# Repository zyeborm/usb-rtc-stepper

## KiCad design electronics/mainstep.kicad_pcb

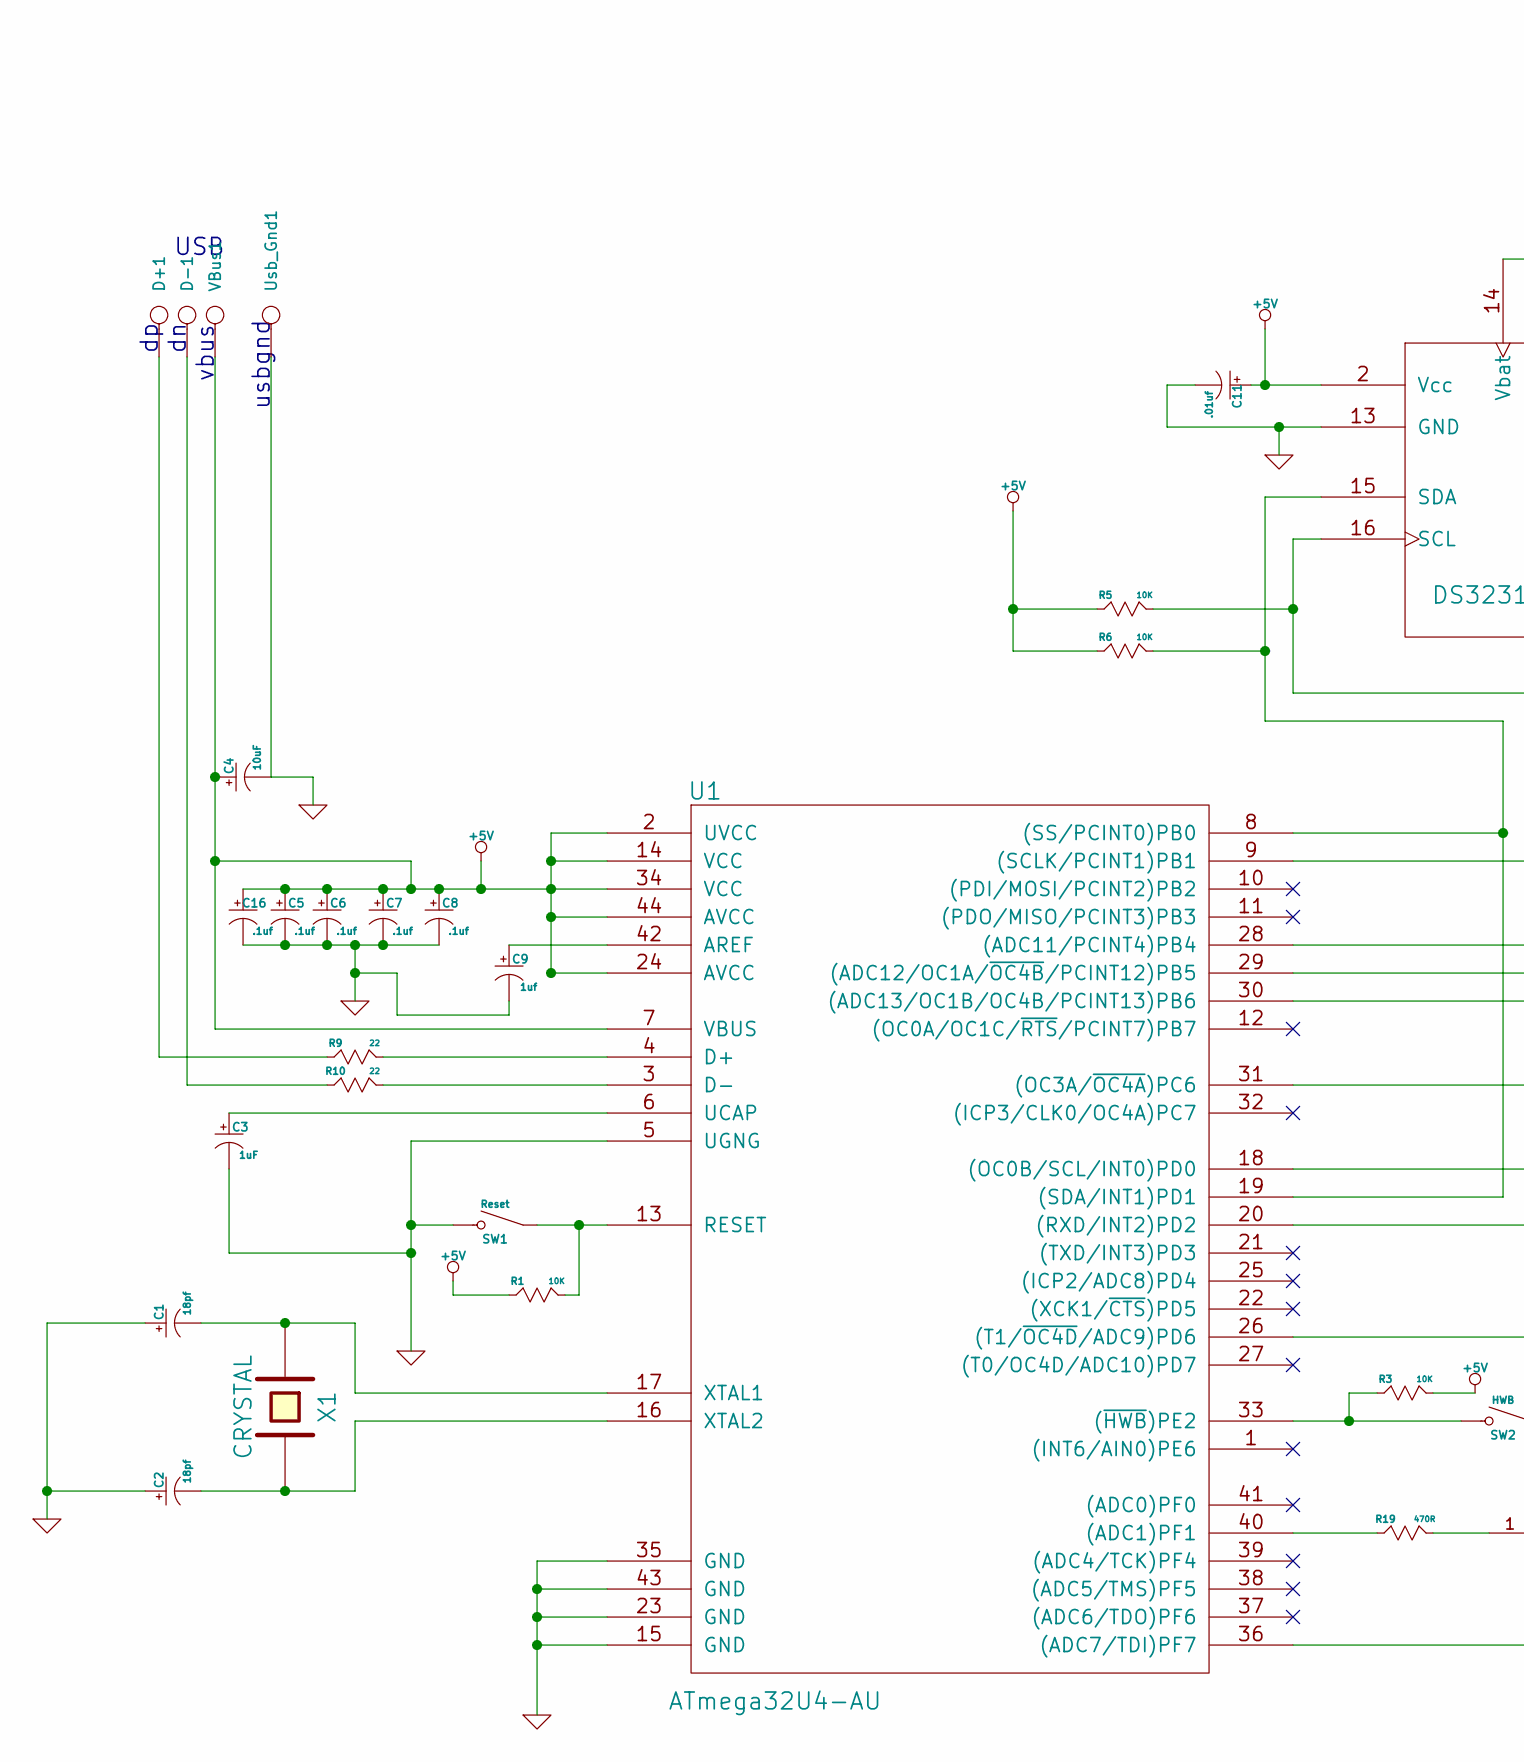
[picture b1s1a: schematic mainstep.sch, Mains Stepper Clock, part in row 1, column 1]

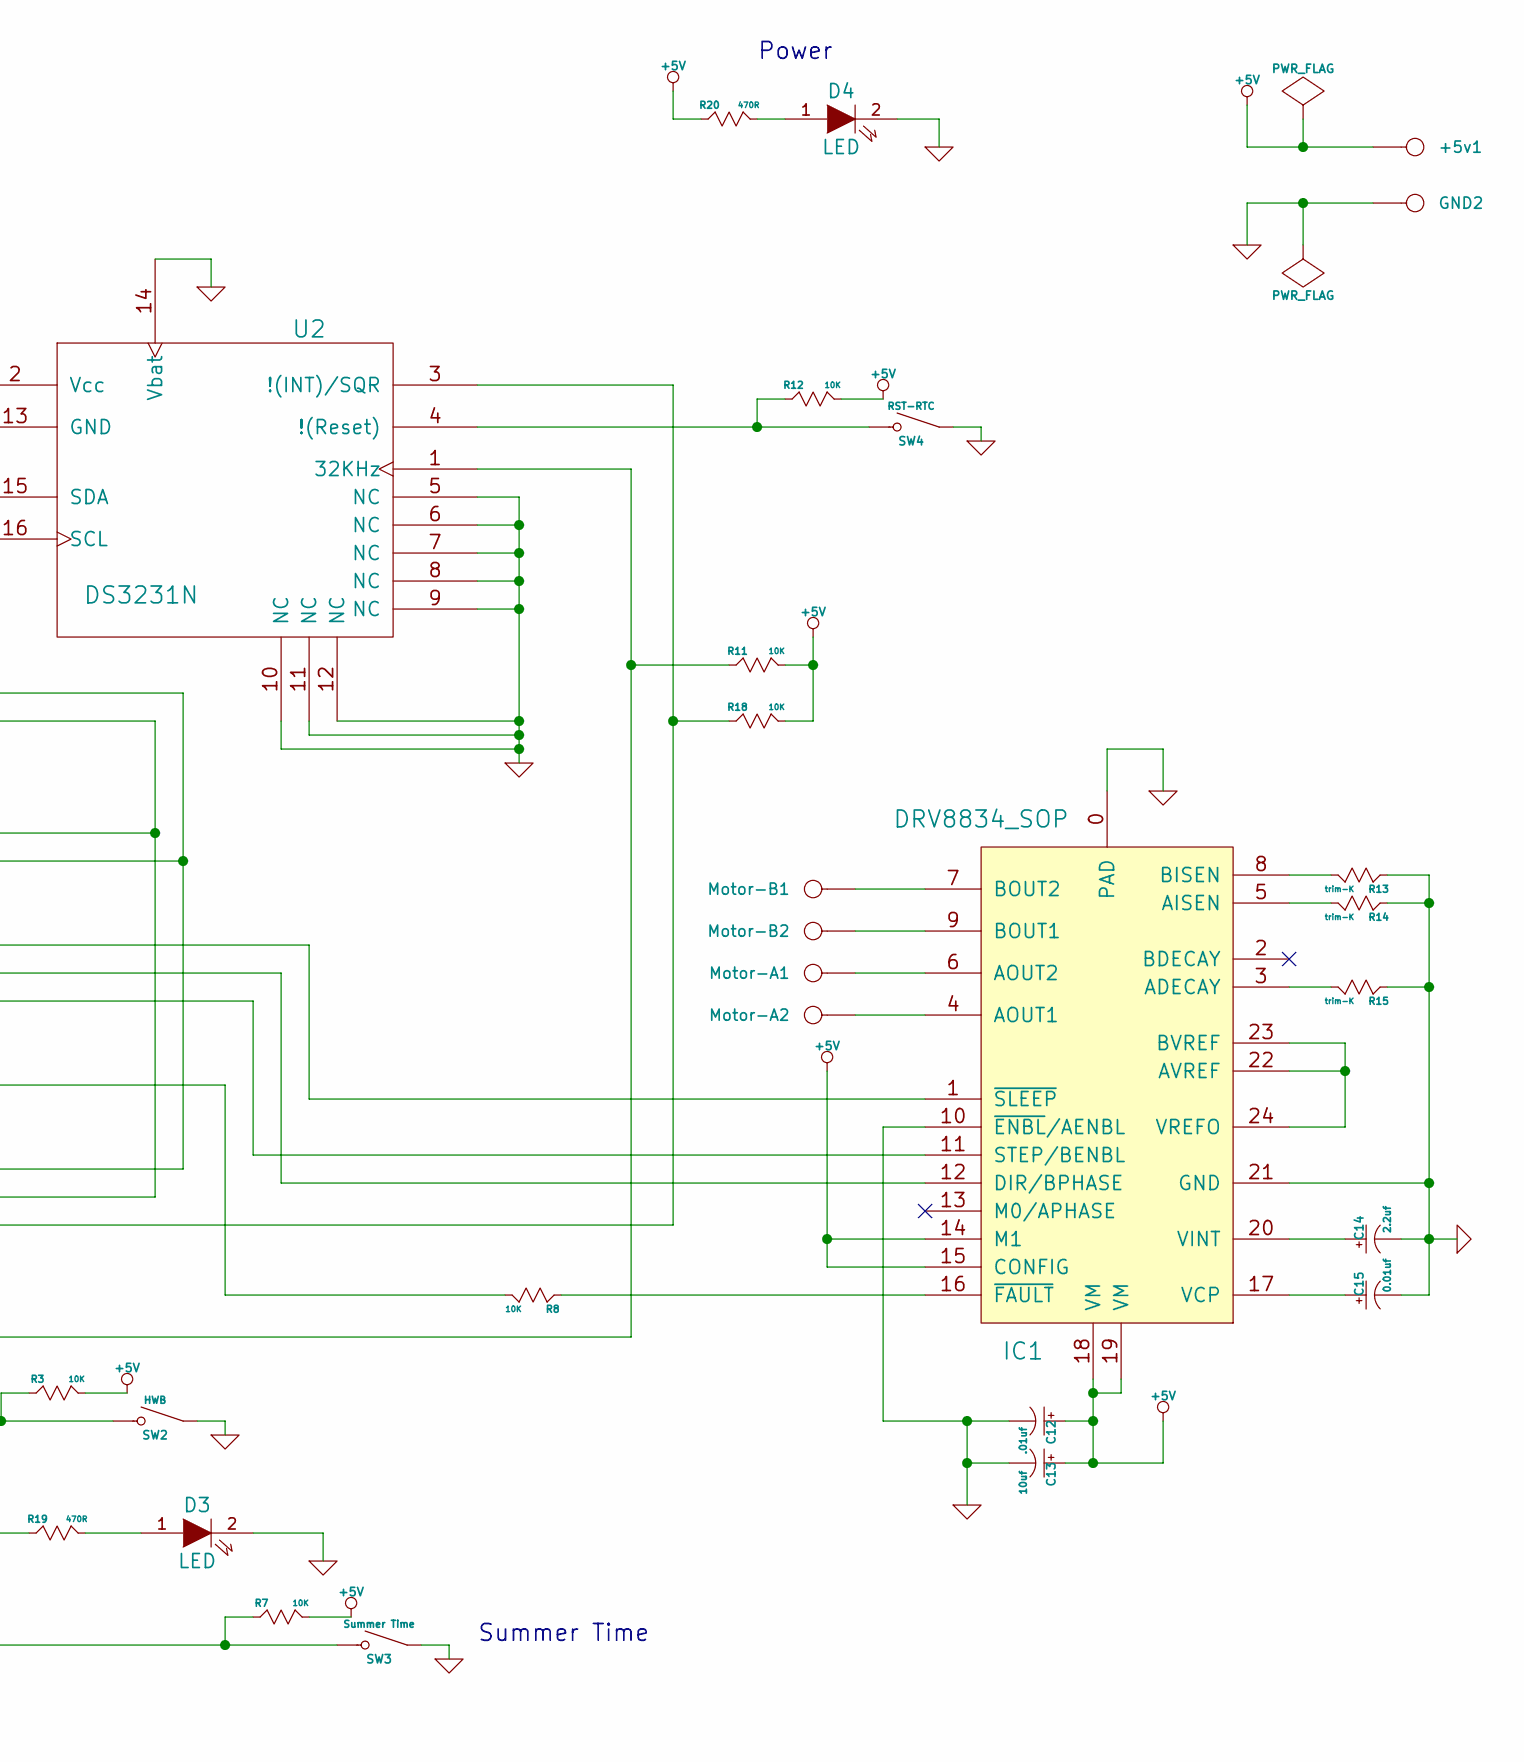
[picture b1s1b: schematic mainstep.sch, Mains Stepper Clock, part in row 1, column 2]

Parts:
+5v1: CONN_1
C1, C2: 18pf
C3: 1uF
C4: 10uF
C5, C6, C7, C8, C16: .1uf
C9: 1uf
C11, C12: .01uf
C13: 10uf
C14: 2.2uf
C15: 0.01uf
D3, D4: LED
D+1: CONN_1
D-1: CONN_1
GND2: CONN_1
IC1: DRV8834_SOP
Motor-A1, Motor-A2: CONN_1
Motor-B1, Motor-B2: CONN_1
R1, R3, R5, R6, R7, R8, R11, R12, R18: 10K
R9, R10: 22
R13, R14, R15: trim-K
R19, R20: 470R
SW1: Reset
SW2: HWB
SW3: Summer Time
SW4: RST-RTC
U1: ATmega32U4-AU
U2: DS3231N
Usb_Gnd1: CONN_1
VBus1: CONN_1
X1: CRYSTAL

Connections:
+5V: +5v1.1, C4.2, C5.2, C6.2, C7.2, C8.2, C11.2, C12.2, C13.2, C16.2, IC1.14 (M1), IC1.15 (CONFIG), IC1.18 (VM), IC1.19 (VM), R1.2 (B), R3.1 (A), R5.2 (B), R6.2 (B), R7.1 (A), R11.1 (A), R12.1 (A), R18.1 (A), R20.2 (B), U1.2 (UVCC), U1.7 (VBUS), U1.14 (VCC), U1.24 (AVCC), U1.34 (VCC), U1.44 (AVCC), U2.2 (Vcc), VBus1.1
GND: C1.2, C2.2, C3.1 (GND), C4.1 (GND), C5.1 (GND), C6.1 (GND), C7.1 (GND), C8.1 (GND), C9.1 (GND), C11.1 (GND), C12.1 (GND), C13.1 (GND), C14.1 (GND), C15.1 (GND), C16.1 (GND), D3.2 (K), D4.2 (K), GND2.1, IC1.0 (PAD), IC1.10 (~ENBL~/AENBL), IC1.21 (GND), R13.2 (B), R14.2 (B), R15.2 (B), SW1.1 (A), SW2.2 (B), SW3.2 (B), SW4.2 (B), U1.5 (UGNG), U1.15 (GND), U1.23 (GND), U1.35 (GND), U1.43 (GND), U2.5 (NC), U2.6 (NC), U2.7 (NC), U2.8 (NC), U2.9 (NC), U2.10 (NC), U2.11 (NC), U2.12 (NC), U2.13 (GND), U2.14 (Vbat), Usb_Gnd1.1
unnamed: C1.1 (GND), U1.17 (XTAL1), X1.1
unnamed: C2.1 (GND), U1.16 (XTAL2), X1.2
unnamed: C3.2, U1.6 (UCAP)
unnamed: C9.2, U1.42 (AREF)
unnamed: C14.2, IC1.20 (VINT)
unnamed: C15.2, IC1.17 (VCP)
unnamed: D3.1 (A), R19.1 (A)
unnamed: D4.1 (A), R20.1 (A)
unnamed: D+1.1, R9.2 (B)
unnamed: D-1.1, R10.2 (B)
unnamed: IC1.1 (~SLEEP~), U1.28 ((ADC11/PCINT4)PB4)
unnamed: IC1.3 (ADECAY), R15.1 (A)
unnamed: IC1.4 (AOUT1), Motor-A2.1
unnamed: IC1.5 (AISEN), R14.1 (A)
unnamed: IC1.6 (AOUT2), Motor-A1.1
unnamed: IC1.7 (BOUT2), Motor-B1.1
unnamed: IC1.8 (BISEN), R13.1 (A)
unnamed: IC1.9 (BOUT1), Motor-B2.1
unnamed: IC1.11 (STEP/BENBL), U1.30 ((ADC13/OC1B/OC4B/PCINT13)PB6)
unnamed: IC1.12 (DIR/BPHASE), U1.29 ((ADC12/OC1A/~OC4B~/PCINT12)PB5)
unnamed: IC1.16 (~FAULT~), R8.2 (B)
unnamed: IC1.22 (AVREF), IC1.23 (BVREF), IC1.24 (VREFO)
unnamed: R1.1 (A), SW1.2 (B), U1.13 (RESET)
unnamed: R3.2 (B), SW2.1 (A), U1.33 ((~HWB~)PE2)
unnamed: R5.1 (A), U1.9 ((SCLK/PCINT1)PB1), U1.18 ((OC0B/SCL/INT0)PD0), U2.16 (SCL)
unnamed: R6.1 (A), U1.8 ((SS/PCINT0)PB0), U1.19 ((SDA/INT1)PD1), U2.15 (SDA)
unnamed: R7.2 (B), SW3.1 (A), U1.36 ((ADC7/TDI)PF7)
unnamed: R8.1 (A), U1.31 ((OC3A/~OC4A~)PC6)
unnamed: R9.1 (A), U1.4 (D+)
unnamed: R10.1 (A), U1.3 (D-)
unnamed: R11.2 (B), U1.26 ((T1/~OC4D~/ADC9)PD6), U2.1 (32KHz)
unnamed: R18.2 (B), U1.20 ((RXD/INT2)PD2), U2.3 (!(INT)/SQR)
unnamed: R19.2 (B), U1.40 ((ADC1)PF1)

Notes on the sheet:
vbus
usbgnd
USB
Summer Time
Power

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
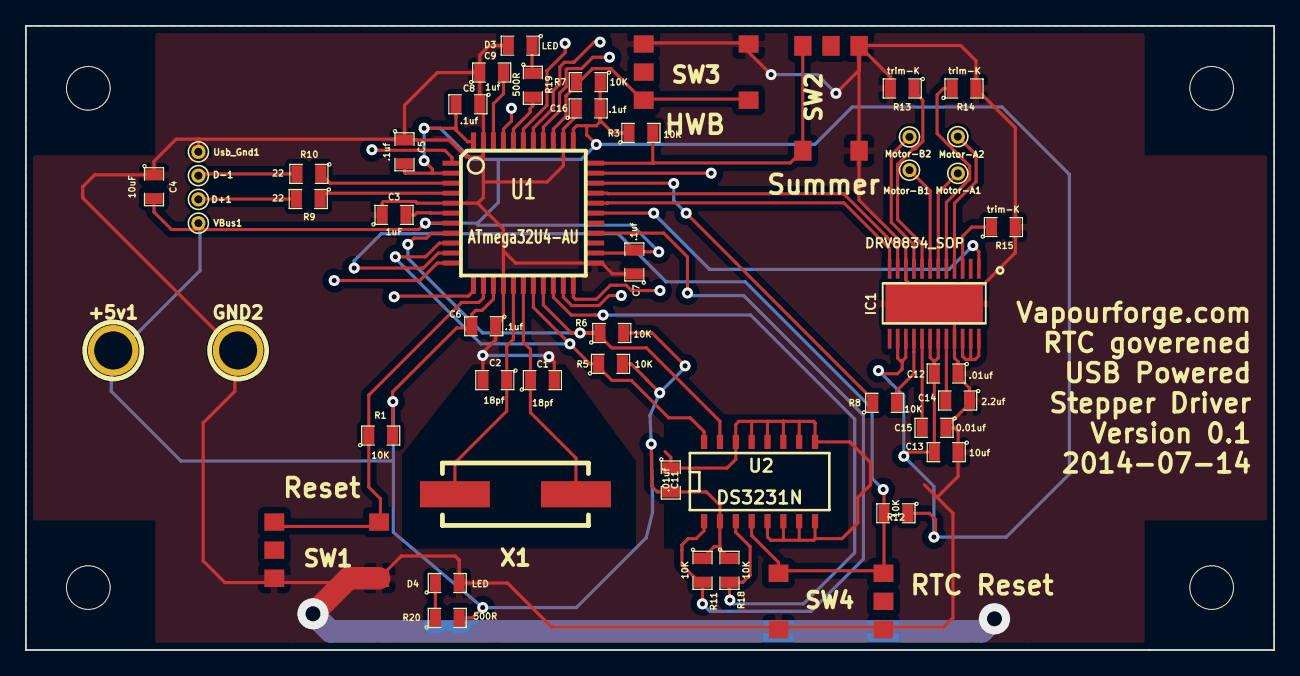
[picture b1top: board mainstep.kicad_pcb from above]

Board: 2 copper layers, 100.0 x 50.0 mm, 51 parts (0 on the bottom side), 36 nets.

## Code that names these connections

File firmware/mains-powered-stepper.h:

/*
             LUFA Library
     Copyright (C) Dean Camera, 2013.

  dean [at] fourwalledcubicle [dot] com
           www.lufa-lib.org
*/

/*
  Copyright 2013  Dean Camera (dean [at] fourwalledcubicle [dot] com)

  Permission to use, copy, modify, distribute, and sell this
  software and its documentation for any purpose is hereby granted
  without fee, provided that the above copyright notice appear in
  all copies and that both that the copyright notice and this
  permission notice and warranty disclaimer appear in supporting
  documentation, and that the name of the author not be used in
  advertising or publicity pertaining to distribution of the
  software without specific, written prior permission.

  The author disclaims all warranties with regard to this
  software, including all implied warranties of merchantability
  and fitness.  In no event shall the author be liable for any
  special, indirect or consequential damages or any damages
  whatsoever resulting from loss of use, data or profits, whether
  in an action of contract, negligence or other tortious action,
  arising out of or in connection with the use or performance of
  this software.
*/

/** \file
 *
 *  Header file for VirtualSerial.c.
 */

#ifndef _VIRTUALSERIAL_H_
#define _VIRTUALSERIAL_H_

	/* Includes: */
		#include <avr/io.h>
		#include <avr/wdt.h>
		#include <avr/power.h>
		#include <avr/interrupt.h>
		#include <string.h>
		#include <stdio.h>
    #include "avr035.h"
		#include "Descriptors.h"

		//#include <LUFA/Drivers/Board/LEDs.h>
		//#include <LUFA/Drivers/Board/Joystick.h>
		#include <LUFA/Drivers/USB/USB.h>

	/* Macros: */
		/** LED mask for the library LED driver, to indicate that the USB interface is not ready. */
		#define LEDMASK_USB_NOTREADY      LEDS_LED1

		/** LED mask for the library LED driver, to indicate that the USB interface is enumerating. */
		#define LEDMASK_USB_ENUMERATING  (LEDS_LED2 | LEDS_LED3)

		/** LED mask for the library LED driver, to indicate that the USB interface is ready. */
		#define LEDMASK_USB_READY        (LEDS_LED2 | LEDS_LED4)

		/** LED mask for the library LED driver, to indicate that an error has occurred in the USB interface. */
		#define LEDMASK_USB_ERROR        (LEDS_LED1 | LEDS_LED3)

	/* Function Prototypes: */
		void SetupHardware(void);
		void CheckJoystickMovement(void);

		void EVENT_USB_Device_Connect(void);
		void EVENT_USB_Device_Disconnect(void);
		void EVENT_USB_Device_ConfigurationChanged(void);
		void EVENT_USB_Device_ControlRequest(void);
		
  #define FLASHER_PORT  PORTF 
  #define FLASHER_PIN   PF1
  #define FLASHER_DDR   DDRF
  #define FLASHER_LED  FLASHER_PORT, FLASHER_PIN  		

  
  #define TIMER1_PWM_PORT  PORTB
  #define TIMER1_PWM_PIN   PB6
  #define TIMER1_PWM_DDR   DDRB
  #define TIMER1_PWM  TIMER1_PWM_PORT, TIMER1_PWM_PIN  		

  #define SLEEP_PORT  PORTB
  #define SLEEP_PIN   PB4
  #define SLEEP_DDR   DDRB
  #define SLEEP_DRV  SLEEP_PORT, SLEEP_PIN  		
  
  #define DIRECTION_PORT  PORTB // ye olde "i'm alive" flasher
  #define DIRECTION_PIN   PB5
  #define DIRECTION_DDR   DDRB
  #define DIRECTION  DIRECTION_PORT, DIRECTION_PIN  		

  #define OUTER_DIRECTION_PORT  PORTB // ye olde "i'm alive" flasher
  #define OUTER_DIRECTION_PIN   PB6
  #define OUTER_DIRECTION_DDR   DDRB
  #define OUTER_DIRECTION  OUTER_DIRECTION_PORT, OUTER_DIRECTION_PIN 
    
  #define TIMER3_PWM_PORT  PORTC // ye olde "i'm alive" flasher
  #define TIMER3_PWM_PIN   PC6
  #define TIMER3_PWM_DDR   DDRC
  #define TIMER3_PWM  TIMER3_PWM_PORT, TIMER3_PWM_PIN  		

#define BT_OUTER_PORT  PORTF  //next (menu) button
#define BT_OUTER_PIN   PF4 
#define BT_OUTER_DDR   DDRF
#define BT_OUTER_OUT  BT_OUTER_PORT, BT_OUTER_PIN
#define BT_OUTER  PINF, BT_OUTER_PIN

#define BT_LEFT_AUX_PORT  PORTE  //next (menu) button
#define BT_LEFT_AUX_PIN   PE6
#define BT_LEFT_AUX_DDR   DDRE
#define BT_LEFT_AUX_OUT  BT_LEFT_AUX_PORT, BT_LEFT_AUX_PIN
#define BT_LEFT_AUX  PINE, BT_LEFT_AUX_PIN

#define BT_RIGHT_AUX_PORT  PORTF  //next (menu) button
#define BT_RIGHT_AUX_PIN   PF7
#define BT_RIGHT_AUX_DDR   DDRF
#define BT_RIGHT_AUX_OUT  BT_RIGHT_AUX_PORT, BT_RIGHT_AUX_PIN
#define BT_RIGHT_AUX  PINF, BT_RIGHT_AUX_PIN

  #define MAN_MODE_PORT  PORTF // ye olde "i'm alive" flasher
  #define MAN_MODE_PIN   PF5
  #define MAN_MODE_DDR   DDRF
  #define MAN_MODE_OUT   MAN_MODE_PORT, MAN_MODE_PIN
  #define MAN_MODE  PINF	, MAN_MODE_PIN

  #define BT_INNER_PORT  PORTF // ye olde "i'm alive" flasher
  #define BT_INNER_PIN   PF6
  #define BT_INNER_DDR   DDRF
  #define BT_INNER_OUT   BT_INNER_PORT, BT_INNER_PIN
  #define BT_INNER  PINF	, BT_INNER_PIN

 /* #define BT_OUTER_PORT  PORTF // ye olde "i'm alive" flasher
  #define BT_OUTER_PIN   PF6
  #define BT_OUTER_DDR   DDRF
  #define BT_OUTER_OUT   BT_OUTER_PORT, BT_OUTER_PIN
  #define BT_OUTER  PINF	, BT_OUTER_PIN
 		*/ 		
  

  
  
#endif

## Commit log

2014-08-07 updated values
    470R led drop resistors
2014-08-21 first round of firmware, blinking lights and slow stepping
2014-08-21 quit kicad
